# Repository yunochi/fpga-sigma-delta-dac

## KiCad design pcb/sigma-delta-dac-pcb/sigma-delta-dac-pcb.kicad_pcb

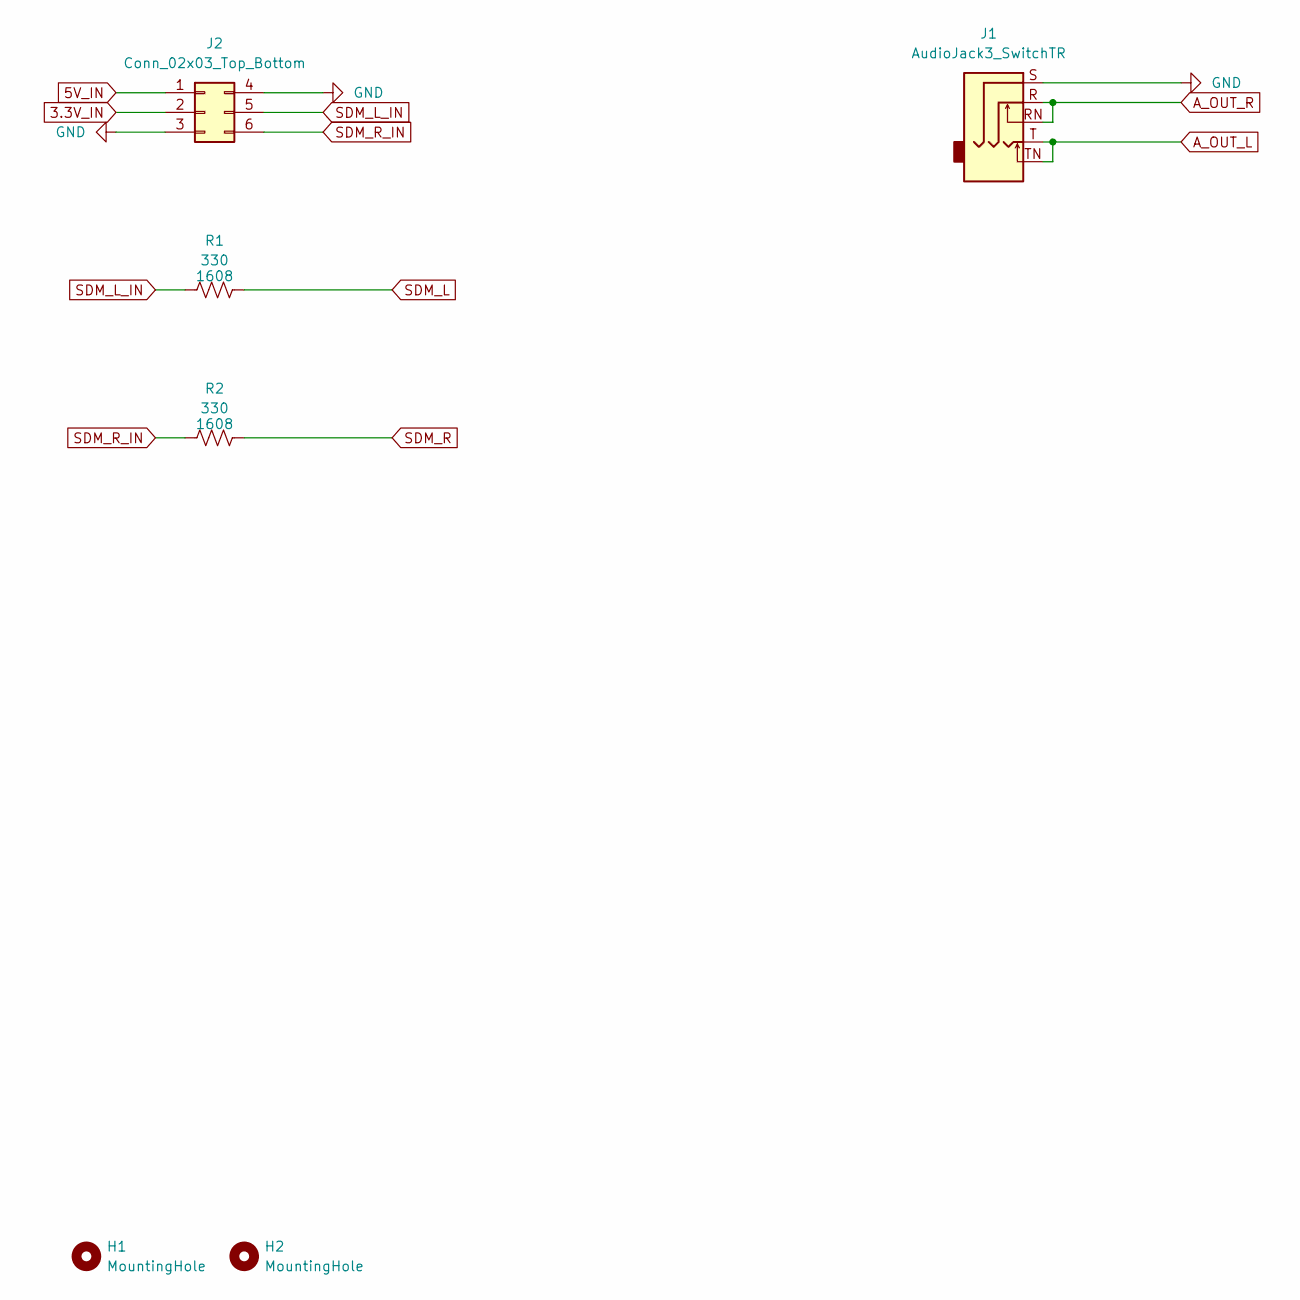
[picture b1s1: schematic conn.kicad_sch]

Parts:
H1, H2: MountingHole; MountingHole_3.2mm_M3
J1: AudioJack3_SwitchTR; Jack_3.5mm_CUI_SJ1-3525N_Horizontal
J2: Conn_02x03_Top_Bottom; PinSocket_2x03_P2.54mm_Vertical
R1, R2: 330; R_0603_1608Metric

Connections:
3.3V_IN: J2.2
5V_IN: J2.1; also elsewhere on the board
A_OUT_L: J1.T, J1.TN; also elsewhere on the board
A_OUT_R: J1.R, J1.RN; also elsewhere on the board
SDM_L: R1.2; also elsewhere on the board
SDM_L_IN: J2.5, R1.1
SDM_R: R2.2; also elsewhere on the board
SDM_R_IN: J2.6, R2.1

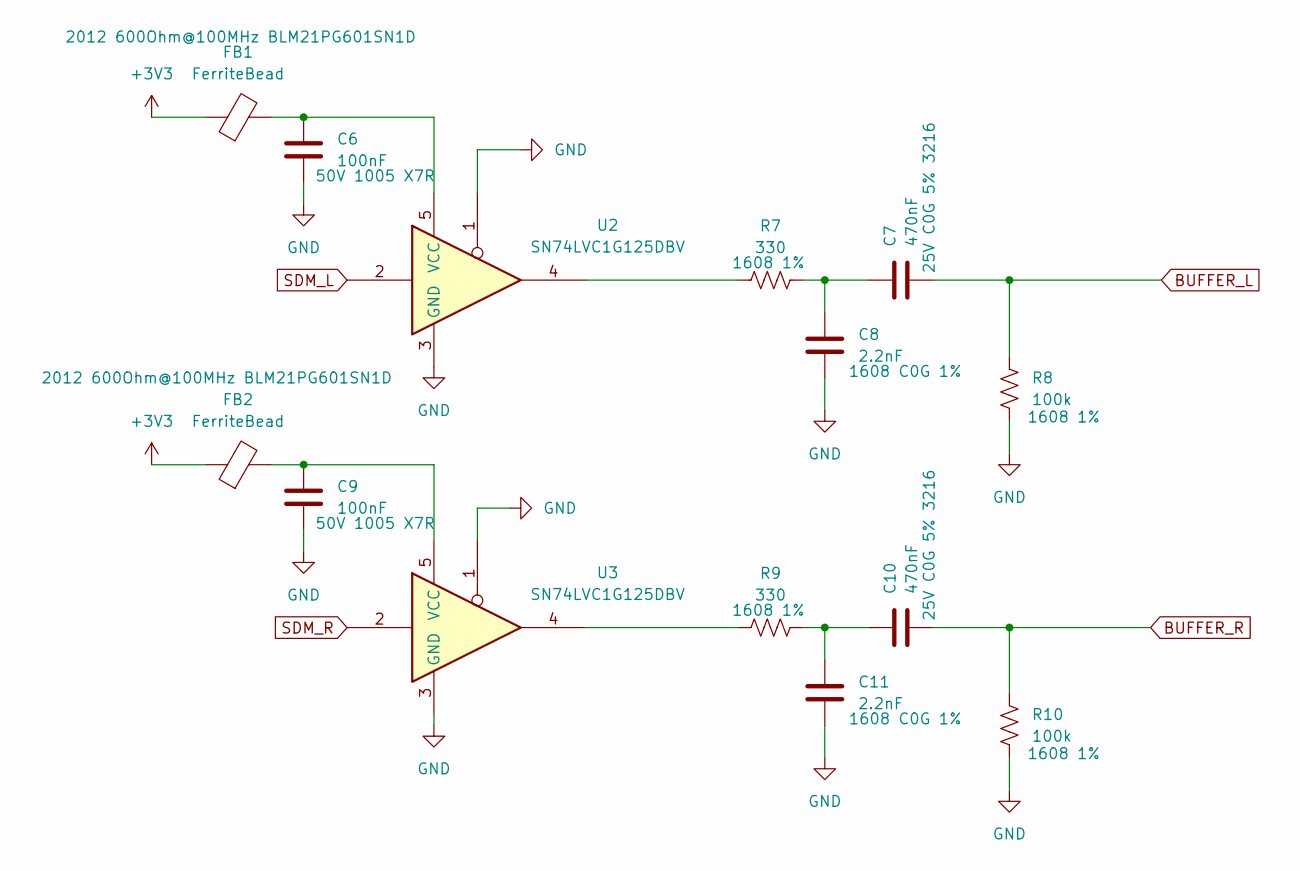
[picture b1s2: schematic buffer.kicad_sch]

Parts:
C6, C9: 100nF; C_0402_1005Metric
C7, C10: 470nF; C_1206_3216Metric
C8, C11: 2.2nF; C_0603_1608Metric
FB1, FB2: FerriteBead; L_0805_2012Metric
R7, R9: 330; R_0603_1608Metric
R8, R10: 100k; R_0603_1608Metric
U2, U3: SN74LVC1G125DBV; SOT-23-5

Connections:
BUFFER_L: C7.2, R8.1; also elsewhere on the board
BUFFER_R: C10.2, R10.1; also elsewhere on the board
unnamed: C7.1, C8.1, R7.2
unnamed: C10.1, C11.1, R9.2
unnamed: R7.1, U2.4
unnamed: R9.1, U3.4
unnamed: C6.1, FB1.2, U2.5 (VCC)
unnamed: C9.1, FB2.2, U3.5 (VCC)
SDM_L: U2.2; also elsewhere on the board
SDM_R: U3.2; also elsewhere on the board

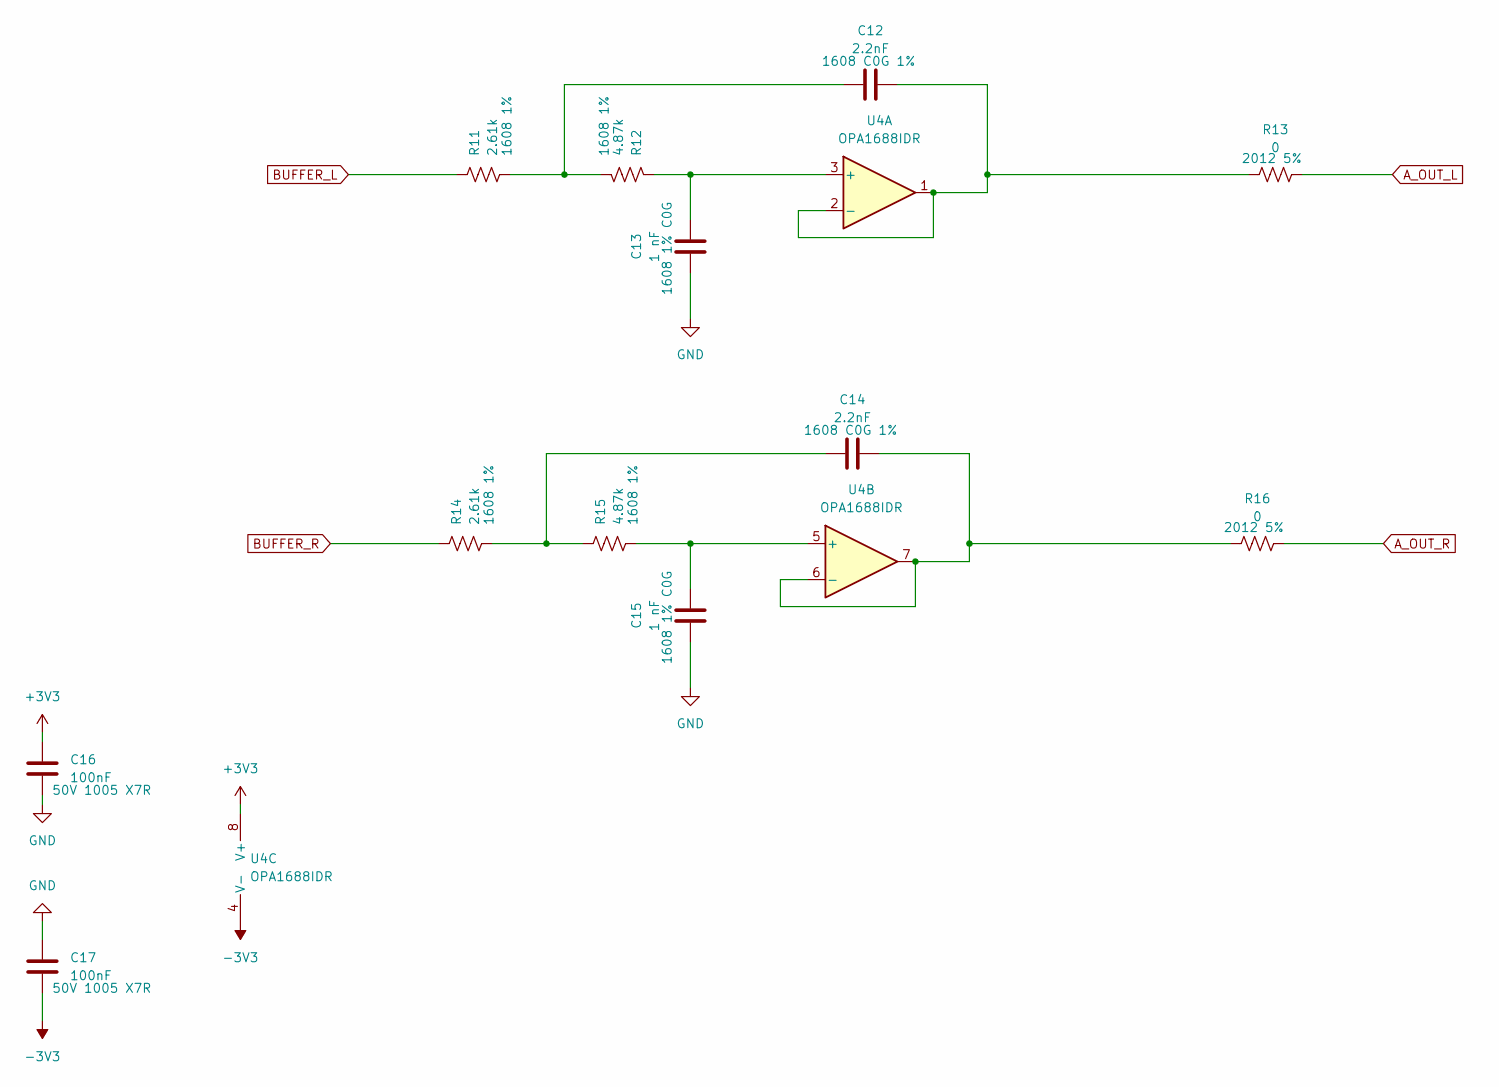
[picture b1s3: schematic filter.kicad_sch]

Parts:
C12, C14: 2.2nF; C_0603_1608Metric
C13, C15: 1 nF; C_0603_1608Metric
C16, C17: 100nF; C_0402_1005Metric
R11, R14: 2.61k; R_0603_1608Metric
R12, R15: 4.87k; R_0603_1608Metric
R13, R16: 0; R_0805_2012Metric
U4: OPA1688IDR; SOIC-8_3.9x4.9mm_P1.27mm

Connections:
A_OUT_L: R13.2; also elsewhere on the board
A_OUT_R: R16.2; also elsewhere on the board
BUFFER_L: R11.1; also elsewhere on the board
BUFFER_R: R14.1; also elsewhere on the board
unnamed: C12.1, R11.2, R12.2
unnamed: C14.1, R14.2, R15.1
unnamed: C13.2, R12.1, U4.3 (+)
unnamed: C12.2, R13.1, U4.1, U4.2 (-)
unnamed: C15.2, R15.2, U4.5 (+)
unnamed: C14.2, R16.1, U4.6 (-), U4.7

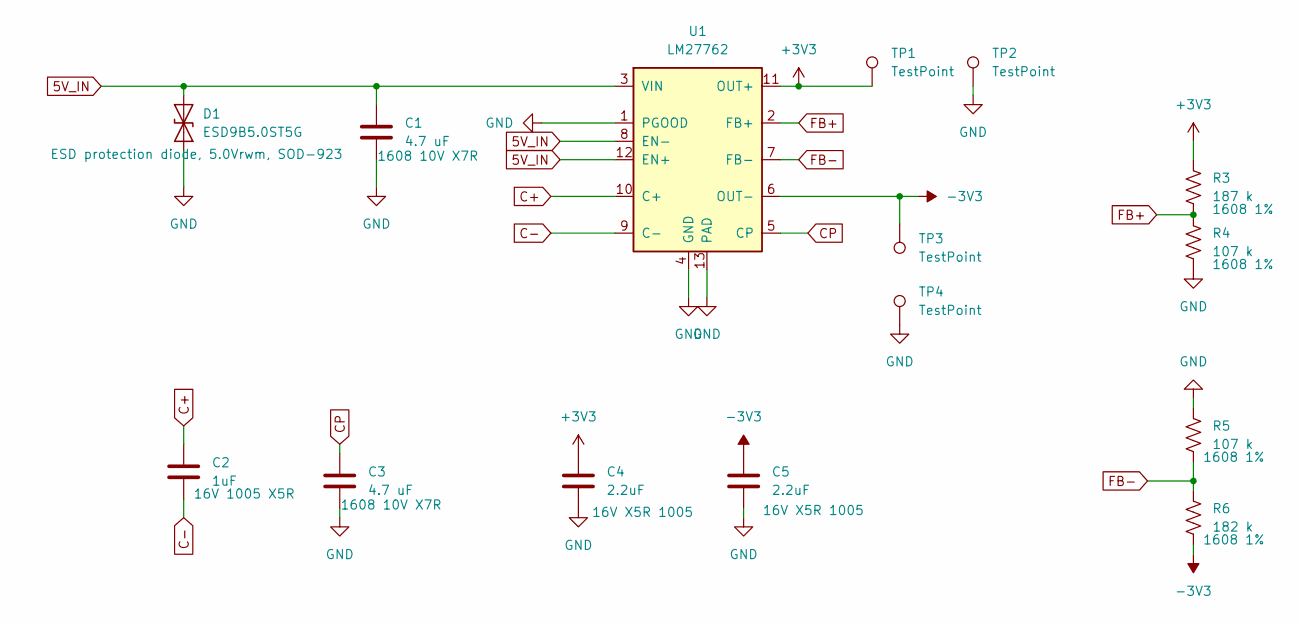
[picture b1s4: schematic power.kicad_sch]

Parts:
C1, C3: 4.7 uF; C_0603_1608Metric
C2: 1uF; C_0402_1005Metric
C4, C5: 2.2uF; C_0402_1005Metric
D1: ESD9B5.0ST5G; D_SOD-923
R3: 187 k; R_0603_1608Metric
R4, R5: 107 k; R_0603_1608Metric
R6: 182 k; R_0603_1608Metric
TP1, TP2, TP3, TP4: TestPoint; TestPoint_Pad_1.0x1.0mm
U1: LM27762; WSON-12-1EP_3x2mm_P0.5mm_EP1x2.65_ThermalVias

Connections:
5V_IN: C1.1, D1.2 (A2), U1.3 (VIN), U1.8 (EN-), U1.12 (EN+); also elsewhere on the board
C+: C2.1, U1.10 (C+)
C-: C2.2, U1.9 (C-)
CP: C3.1, U1.5 (CP)
FB+: R3.2, R4.1, U1.2 (FB+)
FB-: R5.2, R6.1, U1.7 (FB-)

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
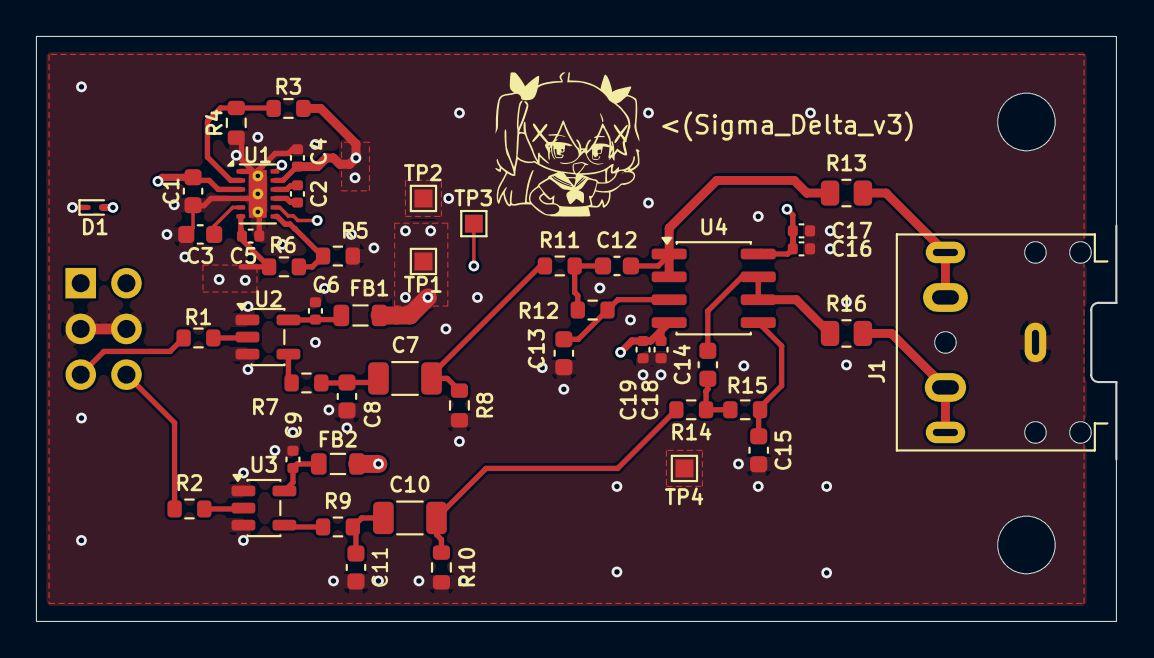
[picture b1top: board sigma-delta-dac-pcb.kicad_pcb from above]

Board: 4 copper layers, 60.0 x 32.4 mm, 50 parts (1 on the bottom side), 29 nets.

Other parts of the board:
C18, C19: 100nF; C_0402_1005Metric

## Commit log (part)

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2026-06-10 init
2026-06-12 pcb 추가
2026-06-12 update gitignore
2026-06-13 ethernet patch 수정
2026-06-15 하프 밴드 FIR필터 추가
2026-06-15 코드 정리
2026-06-16 OPAMP 출력단 저항 수정
2026-06-16 회로도 수정: 50옴 롤백, OPAMP전원 캡 증가
2026-06-17 FPGA 로직 96kHz 입력 + 선형보간으로 변경
2026-06-18 시뮬레이션 수정
2026-06-22 v2 회로 - wip
2026-06-22 Via 추가
2026-06-23 로직 클럭을 온보드 200MHz 클럭 쓰도록 변경
2026-06-24 V2 보드 완성
2026-06-30 63탭 FIR필터로 변경
2026-06-30 입력 샘플레이트 48kHz, FIR 필터 사용
2026-06-30 파이프라이닝 적용. 곱셈기 감소
2026-06-30 tb 코드 분리
2026-06-30 Refactor
2026-06-30 FPGA 코드 리팩토링.
    - 모듈별 파일 분리
    - pcm_in_l, pcm_in_r 레지스터 추가
